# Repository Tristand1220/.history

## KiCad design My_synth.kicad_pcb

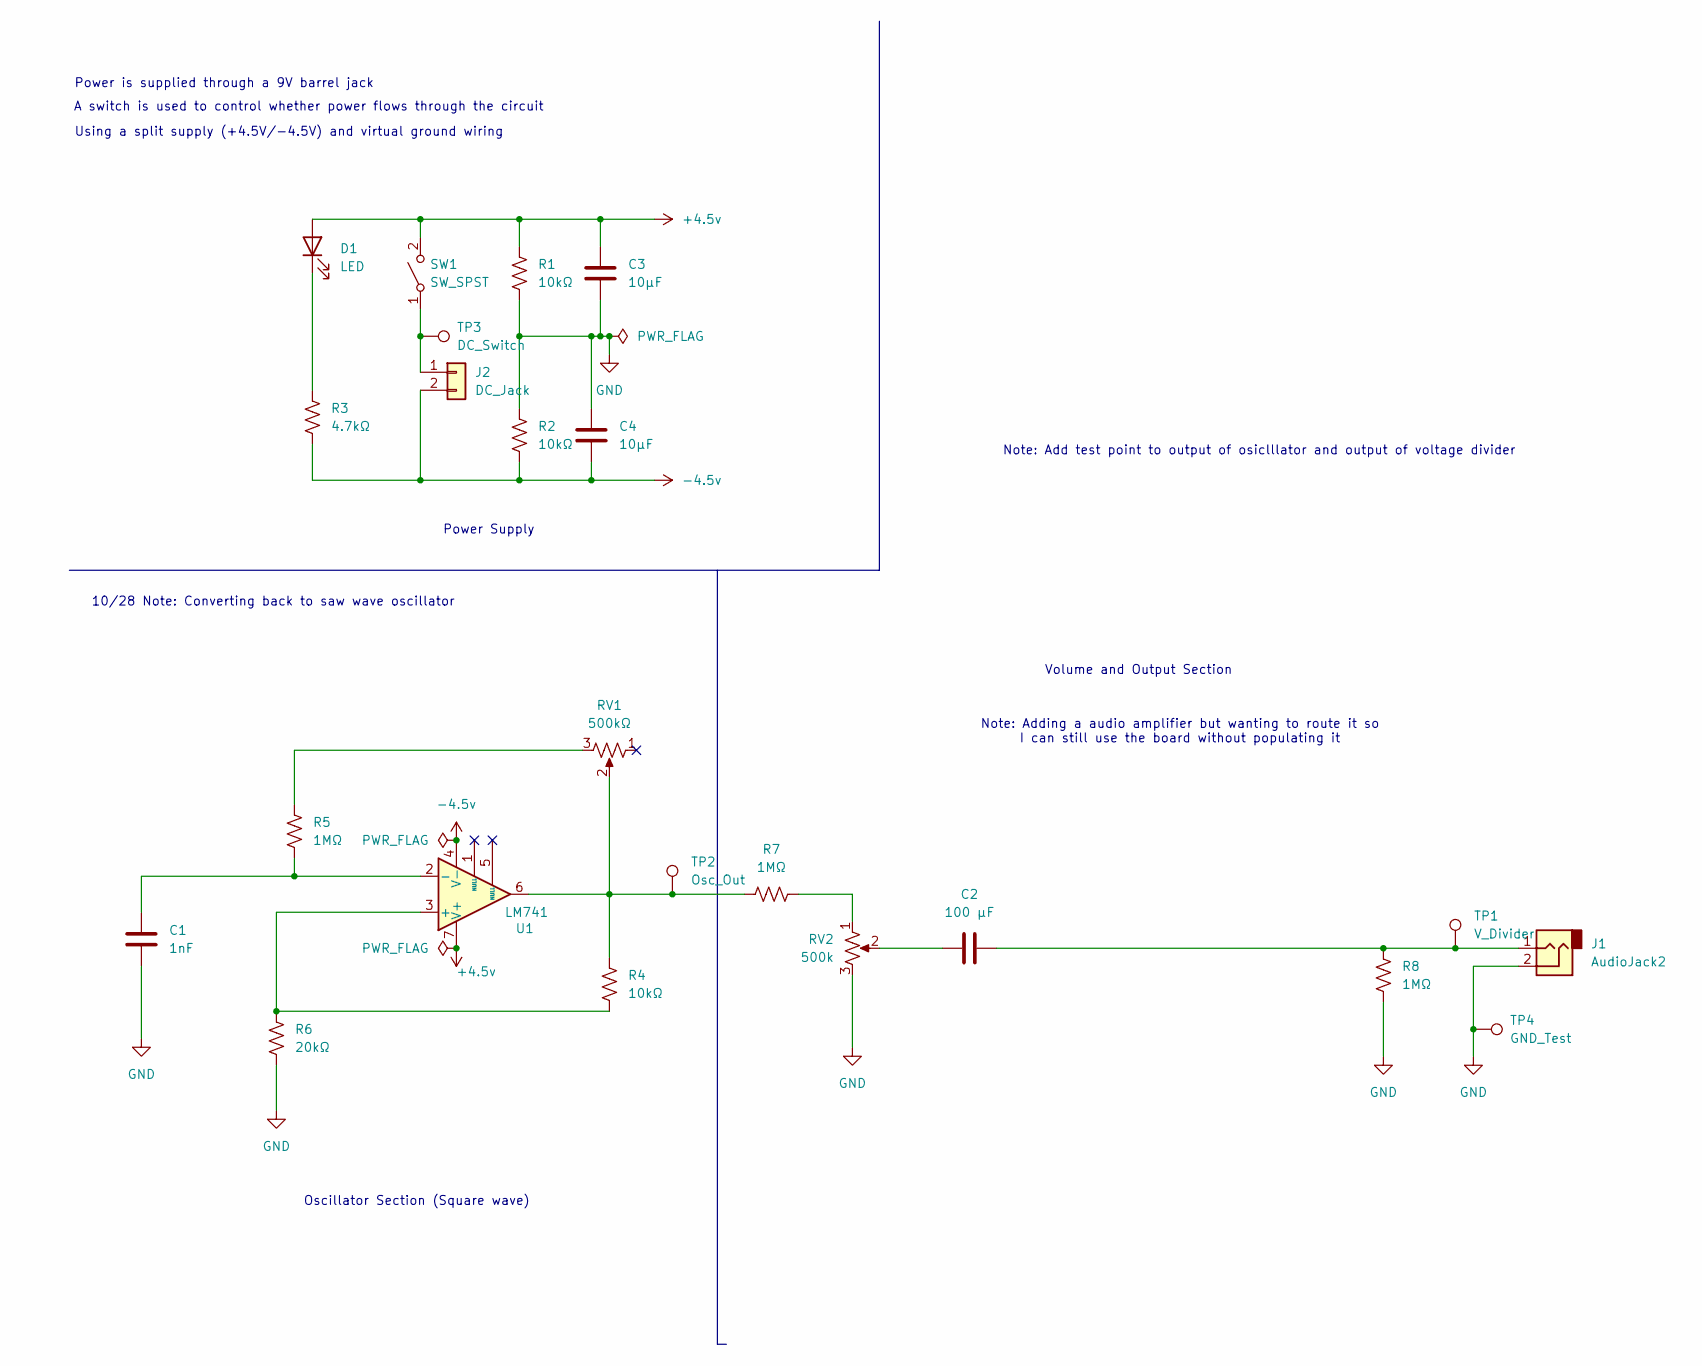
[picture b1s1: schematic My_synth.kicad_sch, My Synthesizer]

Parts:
C1: 1nF; C_0603_1608Metric_Pad1.08x0.95mm_HandSolder
C2: 100 μF; C_1210_3225Metric
C3, C4: 10μF; C_0603_1608Metric_Pad1.08x0.95mm_HandSolder
D1: LED; LED_D5.0mm
J1: AudioJack2; SolderWire-0.5sqmm_1x02_P4.6mm_D0.9mm_OD2.1mm
J2: DC_Jack; SolderWire-0.5sqmm_1x02_P4.8mm_D0.9mm_OD2.3mm
R1, R2, R4: 10kΩ; R_Axial_DIN0207_L6.3mm_D2.5mm_P7.62mm_Horizontal
R3: 4.7kΩ; R_Axial_DIN0207_L6.3mm_D2.5mm_P7.62mm_Horizontal
R5, R7, R8: 1MΩ; R_Axial_DIN0207_L6.3mm_D2.5mm_P7.62mm_Horizontal
R6: 20kΩ; R_Axial_DIN0207_L6.3mm_D2.5mm_P7.62mm_Horizontal
RV1: 500kΩ; PinHeader_1x03_P2.54mm_Vertical
RV2: 500k; PinHeader_1x03_P2.54mm_Vertical
SW1: SW_SPST; SolderWire-0.5sqmm_1x02_P4.8mm_D0.9mm_OD2.3mm
TP1: V_Divider; TestPoint_Pad_D1.0mm
TP2: Osc_Out; TestPoint_Pad_D1.0mm
TP3: DC_Switch; TestPoint_Pad_D1.0mm
TP4: GND_Test; TestPoint_Pad_D1.0mm
U1: LM741; DIP-8_W7.62mm_Socket

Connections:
+4.5v: C3.1, D1.2 (A), R1.1, SW1.2 (B), U1.7 (V+)
-4.5v: C4.2, J2.2, R2.2, R3.2, U1.4 (V-)
GND: C1.2, C3.2, C4.1, J1.2, R1.2, R2.1, R6.2, R8.1, RV2.3, TP4.1 (1_1)
unnamed: C2.1, RV2.2
unnamed: C2.2, J1.1, R8.2, TP1.1 (1_1)
unnamed: D1.1 (K), R3.1
unnamed: J2.1, SW1.1 (A), TP3.1 (1_1)
unnamed: R4.1, R7.2, RV1.2, TP2.1 (1_1), U1.6
unnamed: R5.2, RV1.3
unnamed: R7.1, RV2.1
unnamed: R4.2, R6.1, U1.3 (+)
unnamed: C1.1, R5.1, U1.2 (-)

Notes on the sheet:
Note: Add test point to output of osiclllator and output of voltage divider
Using a split supply (+4.5V/-4.5V) and virtual ground wiring
Power Supply
Volume and Output Section
A switch is used to control whether power flows through the circuit
Oscillator Section (Square wave)
Note: Adding a audio amplifier but wanting to route it so I can still use the board without populating it
Power is supplied through a 9V barrel jack
10/28 Note: Converting back to saw wave oscillator

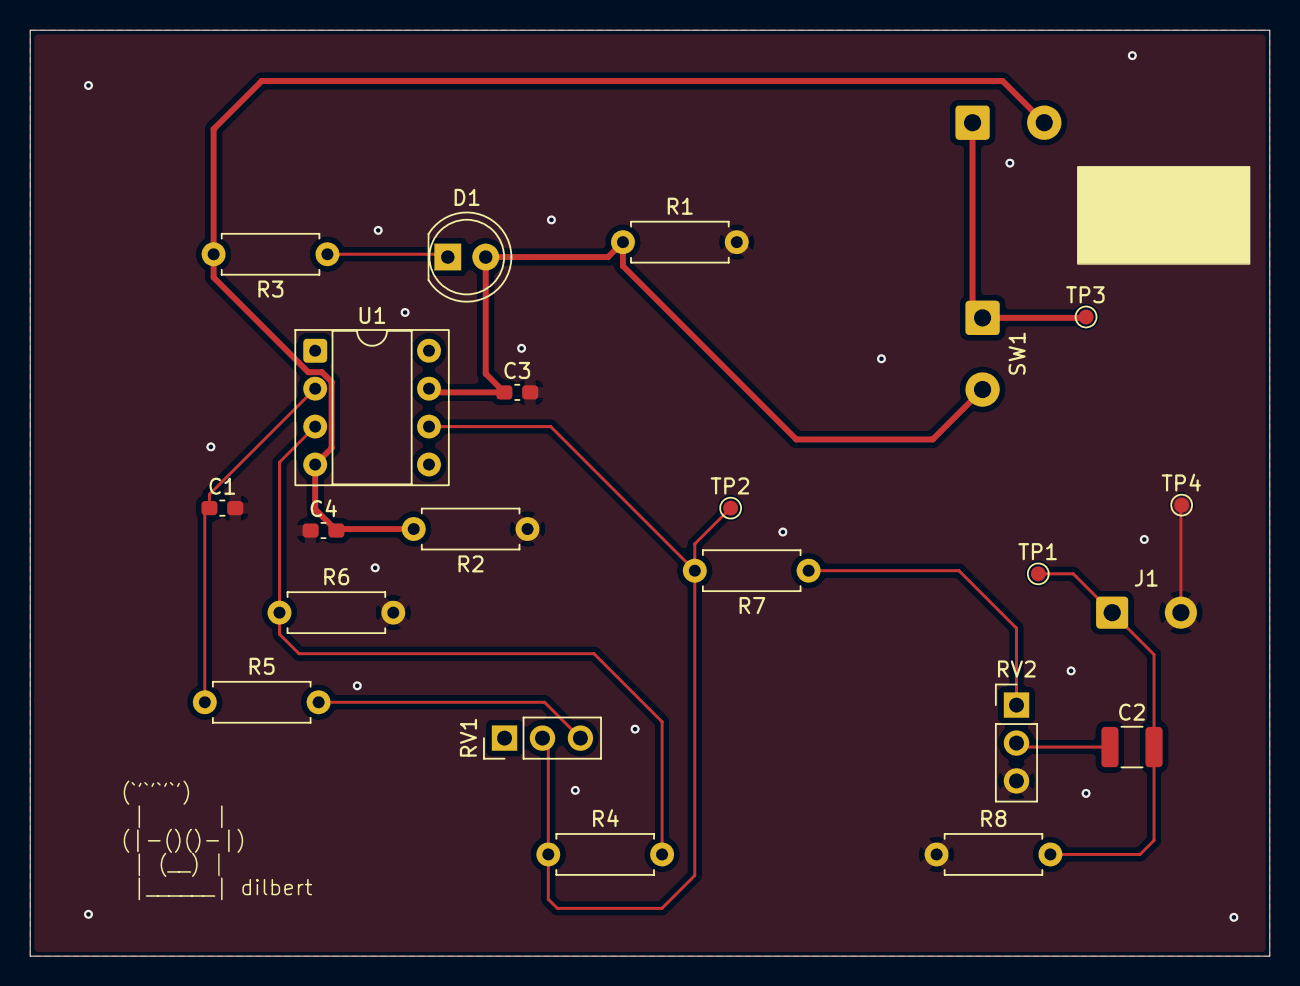
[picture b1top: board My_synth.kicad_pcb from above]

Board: 2 copper layers, 83.0 x 62.0 mm, 23 parts (0 on the bottom side), 12 nets.
